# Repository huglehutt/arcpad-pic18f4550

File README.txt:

ARCPAD
projet de création d'un pad d'arcade sur base Pic18f4550

********************
-----SOURCES--------

contien les sources (C,ASM,... et Hex filles)
nessessite MPLab 8.91+ (Microchip)
nessessite C18 compiler for MPLab(Microchip)

tout les fichiers source sont propriété de microchip et s'applique dessus les Licenses et droit des auteurs.

seul les fichiers :
- joypad_map.c 
- joypad_map.h
sont entièrement libre

********************
-----BOARD----------
fichiers eagle
contien les plans du circuit imprimé : 
- traversant
- version 2 joueurs.

********************
-----3D-2D---------
fichier SOLIDWORK
fichier INKSCAPE (pour decoupe laser)

pour plus d'info : labboite.fr
sujet arcade du wiki 
http://documentation.labboite.fr/xwiki

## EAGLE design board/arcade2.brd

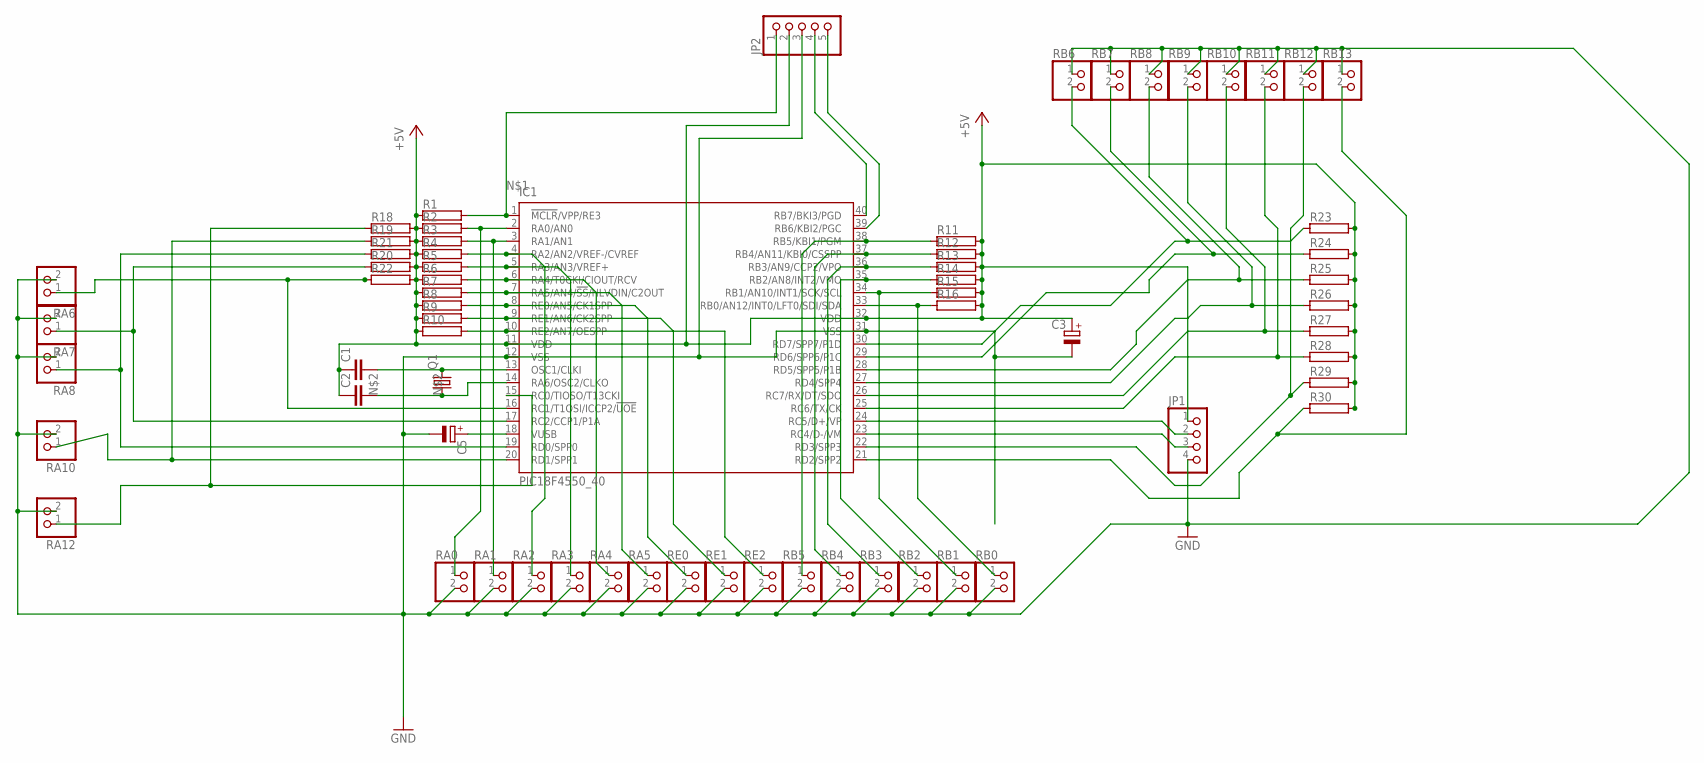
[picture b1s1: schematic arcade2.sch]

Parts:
C1, C2: C10/4; C10B4
C3, C5: CPOL-EUB45181C; B45181C
IC1: PIC18F4550_40; DIL40
JP1: PINHD-1X4/90; 1X04/90
JP2: PINHD-1X5/90; 1X05/90
Q1: CRYSTALHC33U-V; HC33U-V
R1, R2, R3, R4, R5, R6, R7, R8, R9, R10, R11, R12, R13, R14, R15, R16, R18, R19, R20, R21, R22, R23, R24, R25, R26, R27, R28, R29, R30: RAC01; AC01
RA0, RA1, RA2, RA3, RA4, RA5, RA6, RA7, RA8, RA10, RA12: PINHD-1X2/90; 1X02/90
RB0, RB1, RB2, RB3, RB4, RB5, RB6, RB7, RB8, RB9, RB10, RB11, RB12, RB13: PINHD-1X2/90; 1X02/90
RE0, RE1, RE2: PINHD-1X2/90; 1X02/90

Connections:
unnamed: IC1.1 (!MCLR!/VPP/RE3), JP2.1, R1.2
unnamed: C2.2, IC1.14 (RA6/OSC2/CLKO), Q1.1
unnamed: IC1.40 (RB7/BKI3/PGD), JP2.4
unnamed: C5.+, IC1.18 (VUSB)
unnamed: IC1.39 (RB6/KBI2/PGC), JP2.5
unnamed: IC1.3 (RA1/AN1), R3.2, RA1.1
unnamed: IC1.24 (RC5/D+/VP), JP1.2
unnamed: IC1.23 (RC4/D-/VM), JP1.3
unnamed: C3.-, C5.-, IC1.12 (VSS), IC1.31 (VSS), JP1.4, JP2.3, RA0.2, RA1.2, RA2.2, RA3.2, RA4.2, RA5.2, RA6.2, RA7.2, RA8.2, RA10.2, RA12.2, RB0.2, RB1.2, RB2.2, RB3.2, RB4.2, RB5.2, RB6.1, RB7.1, RB8.1, RB9.1, RB10.1, RB11.1, RB12.1, RB13.1, RE0.2, RE1.2, RE2.2
unnamed: IC1.2 (RA0/AN0), R2.2, RA0.1
unnamed: IC1.4 (RA2/AN2/VREF-/CVREF), R4.2, RA2.1
unnamed: IC1.7 (RA5/AN4/!SS!/HLVDIN/C2OUT), R7.2, RA5.1
unnamed: IC1.9 (RE1/AN6/CK2SPP), R9.2, RE1.1
unnamed: IC1.38 (RB5/KBI1/PGM), R11.1, RB5.1
unnamed: IC1.37 (RB4/AN11/KBI0/CSSPP), R12.1, RB4.1
unnamed: IC1.36 (RB3/AN9/CCP2/VPO), R13.1, RB3.1
unnamed: IC1.35 (RB2/AN8/INT2/VMO), R14.1, RB2.1
unnamed: IC1.34 (RB1/AN10/INT1/SCK/SCL), R15.1, RB1.1
unnamed: IC1.6 (RA4/T0CKI/CIOUT/RCV), R6.2, RA4.1
unnamed: IC1.10 (RE2/AN7/OESPP), R10.2, RE2.1
unnamed: IC1.5 (RA3/AN3/VREF+), R5.2, RA3.1
unnamed: IC1.30 (RD7/SPP7/P1D), R23.1, RB6.2
unnamed: IC1.28 (RD5/SPP5/P1B), R25.1, RB8.2
unnamed: IC1.29 (RD6/SPP6/P1C), R24.1, RB7.2
unnamed: IC1.27 (RD4/SPP4), R26.1, RB9.2
unnamed: IC1.25 (RC6/TX/CK), R28.1, RB11.2
unnamed: IC1.15 (RC0/TIOSO/T13CKI), R18.1, RA12.1
unnamed: C1.1, C2.1, C3.+, IC1.11 (VDD), IC1.32 (VDD), JP1.1, JP2.2, R1.1, R2.1, R3.1, R4.1, R5.1, R6.1, R7.1, R8.1, R9.1, R10.1, R11.2, R12.2, R13.2, R14.2, R15.2, R16.2, R18.2, R19.2, R20.2, R21.2, R22.2, R23.2, R24.2, R25.2, R26.2, R27.2, R28.2, R29.2, R30.2
unnamed: C1.2, IC1.13 (OSC1/CLKI), Q1.2
unnamed: IC1.22 (RD3/SPP3), R29.1, RB12.2
unnamed: IC1.21 (RD2/SPP2), R30.1, RB13.2
unnamed: IC1.20 (RD1/SPP1), R19.1, RA10.1
unnamed: IC1.33 (RB0/AN12/INT0/LFT0/SDI/SDA), R16.1, RB0.1
unnamed: IC1.8 (RE0/AN5/CK1SPP), R8.2, RE0.1
unnamed: IC1.19 (RD0/SPP0), R21.1, RA8.1
unnamed: IC1.17 (RC2/CCP1/P1A), R20.1, RA7.1
unnamed: IC1.16 (RC1/T1OSI/ICCP2/!UOE), R22.1, RA6.1
unnamed: IC1.26 (RC7/RX/DT/SDO), R27.1, RB10.2

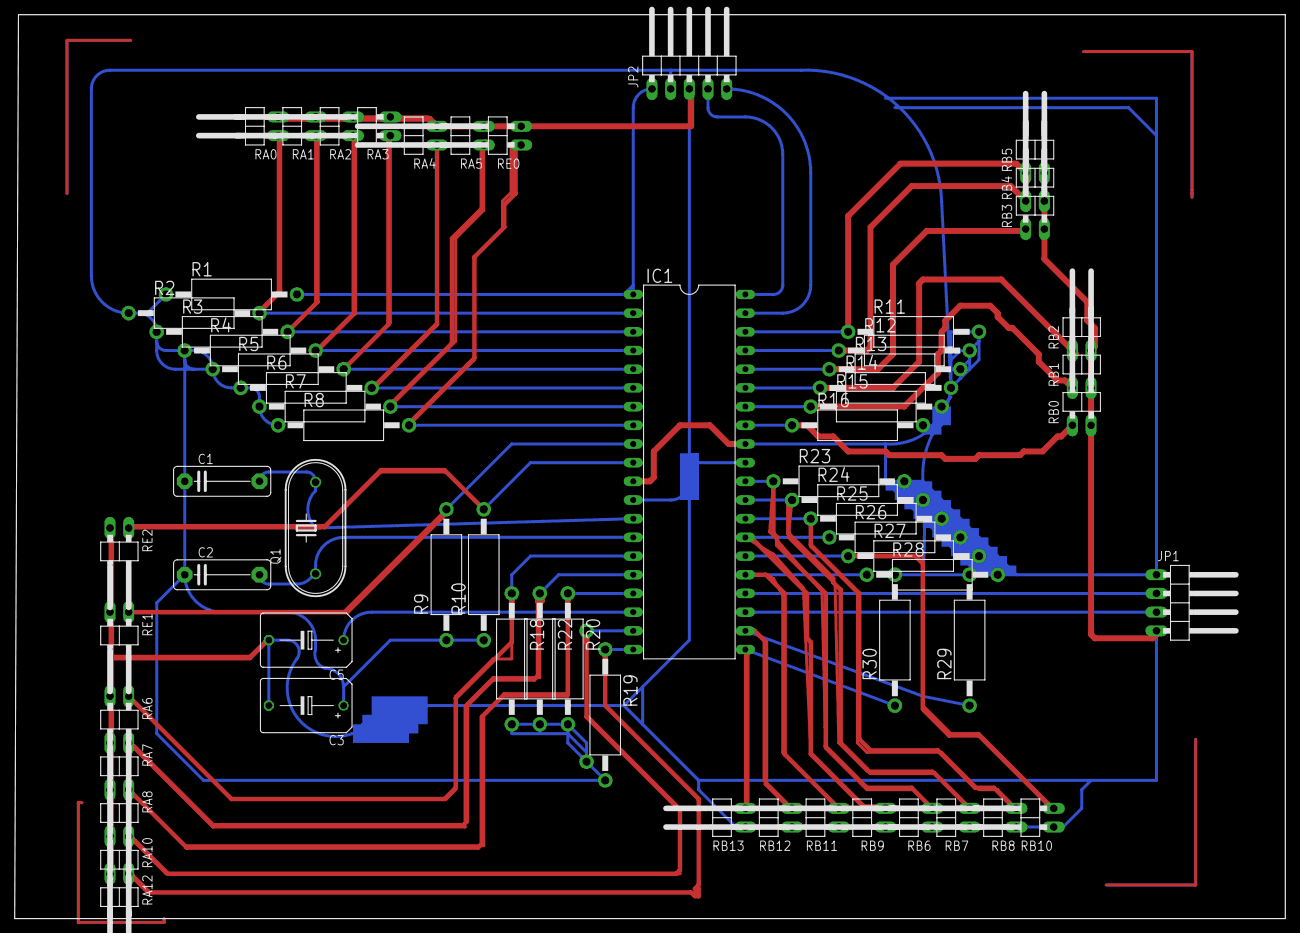
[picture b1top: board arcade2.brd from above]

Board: 2 copper layers, 172.7 x 122.9 mm, 65 parts (1 on the bottom side), 38 nets.

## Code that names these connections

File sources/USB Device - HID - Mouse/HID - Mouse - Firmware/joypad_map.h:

/*Joypad_map.h
* associe les boutons et annalogues au pin du pic
*active les pin du pics
*/

#ifndef JOYPAD_MAP_H
#define JOYPAD_MAP_H

void Init_Joypad(void);
char Lect_AN0(void);
char Lect_AN1(void);
char Lect_1x(void);
char Lect_1y(void);
char Lect_2x(void);
char Lect_2y(void);
char Lect_buton_0_to_7 (void);
char Lect_buton_8_to_15 (void);
char Lect_buton_16_to_23 (void);


  union analogout
  {
    int val;
    struct 
    {
      	unsigned bit0:1;
      	unsigned bit1:1;
      	unsigned bit2:1;
		unsigned bit3:1;
		unsigned bit4:1;
		unsigned bit5:1;
		unsigned bit6:1;
		unsigned bit7:1;

      	unsigned bit8:1;
      	unsigned bit9:1;
      	unsigned bit10:1;
		unsigned bit11:1;
		unsigned bit12:1;
		unsigned bit13:1;
		unsigned bit14:1;
		unsigned bit15:1;


    }charcut;
  };
  typedef union charout
  {
    unsigned char val;
    struct 
    {
      	unsigned bit0:1;
      	unsigned bit1:1;
      	unsigned bit2:1;
		unsigned bit3:1;
		unsigned bit4:1;
		unsigned bit5:1;
		unsigned bit6:1;
		unsigned bit7:1;

    }charcut;
  }charout;


#define buton0 PORTAbits.RA0
#define buton1 PORTAbits.RA1
#define buton2 PORTAbits.RA2
#define buton3 PORTAbits.RA3
#define buton4 PORTAbits.RA4
#define buton5 PORTAbits.RA5

#define buton6 PORTBbits.RB0
#define buton7 PORTBbits.RB1
#define buton8 PORTBbits.RB2
#define buton9 PORTBbits.RB3
#define buton10 PORTBbits.RB4
#define buton11 PORTBbits.RB5

#define buton12 PORTCbits.RC0
#define buton13 PORTCbits.RC1
#define buton14 PORTCbits.RC2
#define buton15 PORTCbits.RC6
#define buton16 PORTCbits.RC7

#define buton17 PORTDbits.RD0
#define buton18 PORTDbits.RD1
#define buton19 PORTDbits.RD2
#define buton20 PORTDbits.RD3
#define buton21 PORTDbits.RD4
#define buton22 PORTDbits.RD5
#define buton23 PORTDbits.RD6
#define buton24 PORTDbits.RD7

#define buton25 PORTEbits.RE2
#define buton26 PORTEbits.RE1
#define buton27 PORTEbits.RE0


#define analogX Lect_AN0()
#define analogY Lect_AN1()






#endif

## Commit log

2017-11-15 Create LICENSE
2017-11-15 add fils of the project
    add fils 1st step
2017-11-15 add sources
    add microchip's sources files
2017-11-15 fin readme
    moila
2018-06-07 correction README.TXT
